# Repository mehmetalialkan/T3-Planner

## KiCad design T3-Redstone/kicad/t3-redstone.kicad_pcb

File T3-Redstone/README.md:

# T3-Redstone

**T3 Gemstone O1 için ROS 2 mobil robot kontrol kartı.**
Gazebo ile aynı yazılımı çalıştıran, TurtleBot sınıfı bir platform.

## Neden

Gemstone O1 güçlü bir bilgisayar ama robot yapmak için üç şeyi yok:

| Eksik | Sonuç |
|---|---|
| **Hiç ADC yok** | Analog sensör, batarya izleme, potansiyometre imkânsız |
| **Motor güç katı yok** | Her takım kendi sürücüsünü breadboard'da kuruyor |
| **7 PWM, ikisi periyot-bağlı** | 50 Hz servo + 400 Hz ESC aynı çipte çalışmıyor |

Redstone bunları ekler ve motor/enkoder işini ESP32-S3'e devrederek Linux'u
gerçek zamanlı kontrol yükünden kurtarır.

## Mimari

```
Gemstone O1 (Linux, ROS 2)              Redstone (ESP32-S3)
├── Nav2 / slam_toolbox                 ├── Tekerlek PID hiz kontrolu
├── ros2_control                        ├── Enkoder sayimi (PCNT, donanim)
│   └── RedstoneHardware ──UART──────>  ├── 16 kanal servo (PCA9685)
├── IMU: ICM-20948 (kartta zaten var)   ├── Batarya izleme (INA226)
└── LiDAR: RPLIDAR USB                  └── Acil stop + watchdog
```

**Kartta zaten olanı tekrar etmiyoruz:** IMU, barometre, RTC, CAN, Wi-Fi/BT,
fan sürücü — hepsi Gemstone'un üstünde.

## Gazebo uyumluluğu

Tek `use_sim` argümanıyla geçiş. Üstteki hiçbir katman değişmez:

```
use_sim:=false -> RedstoneHardware (SystemInterface) -> UART -> ESP32
use_sim:=true  -> gz_ros2_control/GazeboSimSystem    -> Gazebo
```

Aynı URDF, aynı `controllers.yaml`, aynı launch:
`diff_drive_controller` (`/cmd_vel` → `/odom` + TF), `joint_state_broadcaster`.

## Mekanik

Gemstone O1'in kendi Fritzing dosyasından ölçüldü — **Raspberry Pi Model B
form faktörü**:

| | Gemstone O1 | Redstone |
|---|---|---|
| Boyut | 85.0 × 56.0 mm | **85.0 × 56.0 mm** (tam boy) |
| Köşe | 3.0 mm | 3.0 mm |
| Delikler | 58 × 49 mm, sol kenardan 3.5 mm | aynı |
| Header | 2×20 erkek | **2×20 dişi soket, yüksek** |

### Kamera / DSI kesiti
Alt kenara açık bir U kesit: FPC kablosu dışarı çıkar, mandala parmak girer,
frezelemesi kolaydır. Şu anki değer `X 40→57 mm, derinlik 14 mm`.
**Bu değerler fotoğraftan tahmin edildi — Gemstone'un J4 (CSI) ve J12 (CSI/DSI)
konnektörlerini kumpasla ölç**, `kicad/rs_design.py` içindeki `CUT` sözlüğünü
güncelle ve `make` ile kartı yeniden üret.

### Yüksek header zorunlu
Tam boy shield, Gemstone'un **USB-A yığını ve RJ45'inin üzerinden geçer**
(~13.5 mm). Bu yüzden 2×20 dişi soket **en az 16 mm geçiş yüksekliğinde**
olmalı ve standoff'lar da aynı boyda seçilmeli. Shield'in ALT yüzeyine
komponent konulmaz.

## Güç — 2S LiPo, kartta buck yok

Gemstone'un DC girişi zaten regülatörlü, ham batarya gerilimini yiyor.
Redstone sadece **sigorta + ters polarite koruması + acil stop ayrımı + servo BEC**
yapar. Ayrıntı: [docs/03-guc-mimarisi.md](docs/03-guc-mimarisi.md)

> ⚠ Gemstone'un DC giriş aralığı iki kaynakta farklı yazıyor (5–12 V vs 5–9 V).
> Çözülene kadar **yalnızca 2S (6.0–8.4 V)** — her iki okumada da güvenli.

## Dosyalar

| Yol | İçerik |
|---|---|
| `kicad/t3-redstone.kicad_pcb` | **Kart** — 4 katman, kırmızı maske, ENIG, yerleşim + güç + sinyal yolları + GND dolgu |
| `kicad/t3-redstone.kicad_sch` | **Şema** — `rs_design.py`'den üretilir, netlist kartla pin pin aynı |
| `kicad/rs_design.py` | **Tek kaynak**: parçalar, footprint'ler, pad → net, yerleşim, güç dağıtımı |
| `kicad/rs_build.py` | Kartı KiCad'in `pcbnew` API'siyle kurar (resmi kütüphane footprint'leri) |
| `kicad/rs_route.py` | Freerouting ile yönlendirme, güç fanout'u, GND dikiş viaları, dolgu, kalan kopuklar için labirent yönlendirici, KiCad DRC |
| `kicad/rs_sch.py` | Şemayı üretir; `--check` şemadan netlist çıkarıp tasarımla karşılaştırır |
| `kicad/rs_bom.py` · `rs_docs.py` · `rs_render.py` | BOM, netlist belgesi, önizleme SVG |
| `kicad/T3RS.pretty` · `T3RS.kicad_sym` | Projeye özel footprint (servo 3×8) ve semboller (DRV8874, servo) |
| `mekanik/t3-redstone-preview.svg` · `.png` | Kartın üstten görünümü (kicad-cli) |
| `mekanik/t3-redstone-outline.dxf` | Kontur + delikler (her CAD'e girer) |
| `bom/bom.csv` | Parça listesi, MPN'li — `rs_design.py`'den üretilir |
| `docs/01-gemstone-o1-analiz.md` | Gemstone O1 donanım analizi, 40-pin tablosu, EQEP, PWM tuzağı |
| `docs/02-pin-plani.md` | Host + ESP32 pin atamaları, I2C adres haritası |
| `docs/03-guc-mimarisi.md` | Güç topolojisi, acil stop zinciri, katman dağılımı |
| `docs/04-netlist.md` | Bütün netlerin bağlantı listesi + pinout doğrulama tablosu (üretilir) |
| `docs/05-revB-degisiklikler.md` | **Rev A'da bulunan hatalar ve düzeltmeler** |

### Yeniden üretmek

```bash
cd kicad
make            # rs_build -> rs_route -> rs_sch --check -> BOM / netlist / önizleme
```

KiCad 7 (`pcbnew` Python modülüyle), Java 25+ ve Freerouting 2.4.1 gerekir
(`FREEROUTING_JAR=...`, Maven Central: `app.freerouting:freerouting:2.4.1`, `-executable.jar`).
Bir pin ya da koordinat değiştirmek için yalnızca `rs_design.py`'yi düzenle.
Dosyalar KiCad 7 biçiminde üretilir; KiCad 8 / 9 açar.

Freerouting her çalıştırmada biraz farklı yol çizer; `rs_route.py` kalan kopuk parçaları
kendi küçük yönlendiricisiyle tamamlar ve sonunda KiCad DRC'yi çalıştırır
(`kicad/build/drc.rpt`). `python3 rs_route.py --no-route` son Freerouting sonucunu
(`build/t3-redstone.ses`) yeniden kullanır — yerleşim değişmediyse aynı kartı birebir üretir.

## Kartın durumu (rev B)

**Bitmiş olanlar**
- Bütün entegre pinleri resmi kütüphaneyle / veri sayfasıyla karşılaştırıldı; rev A'daki
  14 kritik hata düzeltildi — liste: [docs/05-revB-degisiklikler.md](docs/05-revB-degisiklikler.md)
- 87 komponent (resmi KiCad footprint'leri), 85 net; yerleşim çakışmasız
- 4 katman: `F.Cu` sinyal + güç dökümleri · `In1.Cu` kesintisiz GND · `In2.Cu` bölünmüş güç
  (VSYS / +5V / +3V3 / VBAT_SW) · `B.Cu` sinyal + GND dolgu
- **Kart tamamen yönlendirildi — KiCad DRC: 0 ihlal, 0 bağlantısız ped, 0 footprint hatası**
  (ipek baskı ve kenar açıklıkları dahil); GND dikiş viaları, F/B GND dolgu
- Dekuplaj kondansatörleri pinlerin yanında: C2 (LDO çıkışı) ve C4 (ESP32 3V3) yönleri,
  C12 (PCA9685) konumu düzeltildi
- +3V3: solda In2 düzlemi, orta ve sağdaki tüketicilere B.Cu omurgası
- Şema üretildi; şemadan çıkan netlist kartla **pin pin aynı**
- Kırmızı lehim maskesi + ENIG stackup'ta tanımlı

**Kalan iş**
- Sipariş öncesi "Doğrulanacaklar" listesi (aşağıda) — özellikle 40-pin header ve montaj
  deliği konumları kumpasla teyit edilmeden üretime gönderme
- KiCad 8/9'da açıp bir kez gözle kontrol + Gerber / delik / CPL çıktıları

## Güç topolojisi

```
XT60 -> F1 -> Q1 ters polarite -> RS1 shunt (INA226) -> VSYS
                                                        |
                    +-------------------+---------------+-----------------+
                    |                   |                                 |
               J3 klemens         U7 5V BEC 3A                     Q2 ACIL STOP
               (Gemstone)          |       |                            |
                              servo rayı  U6 3V3 LDO           VBAT_SW -> DRV8874 x2
                              LED, enkoder  -> ESP32, mantık
```

Q2 arızada **kapalıdır**: gate VSYS'e pull-up'lı. Motorlar ancak ESP32 Q3'ü sürerken
**ve** J12'deki NC acil stop butonu kapalıyken güç alır. Ayrıntı:
[docs/03-guc-mimarisi.md](docs/03-guc-mimarisi.md).

## Doğrulanacaklar (sipariş öncesi)

1. **Gemstone DC giriş aralığı** — 5–9 V mı 5–12 V mi? (T3'e sor / e-fuse MPN'ine bak)
2. **40-pin header konumu** — el yapımı Fritzing parçasından ölçüldü, kumpasla teyit et
3. **Montaj delikleri** — layout PDF'inde MH1..MH7 var, Fritzing sadece 4'ünü çiziyor
4. **Stacking header yüksekliği** — Gemstone'un üst yüzeyindeki en yüksek eleman ölçülmeli
5. **Kamera kesiti** — `CUT` değerleri fotoğraftan tahmin
6. **DRV8874 pinout'u** — KiCad kütüphanesinde yok; TI veri sayfasıyla bir kez daha karşılaştır
7. **XT60 cinsiyeti** — kart tarafı bataryanın fişinin karşılığı olmalı (BOM: dişi)

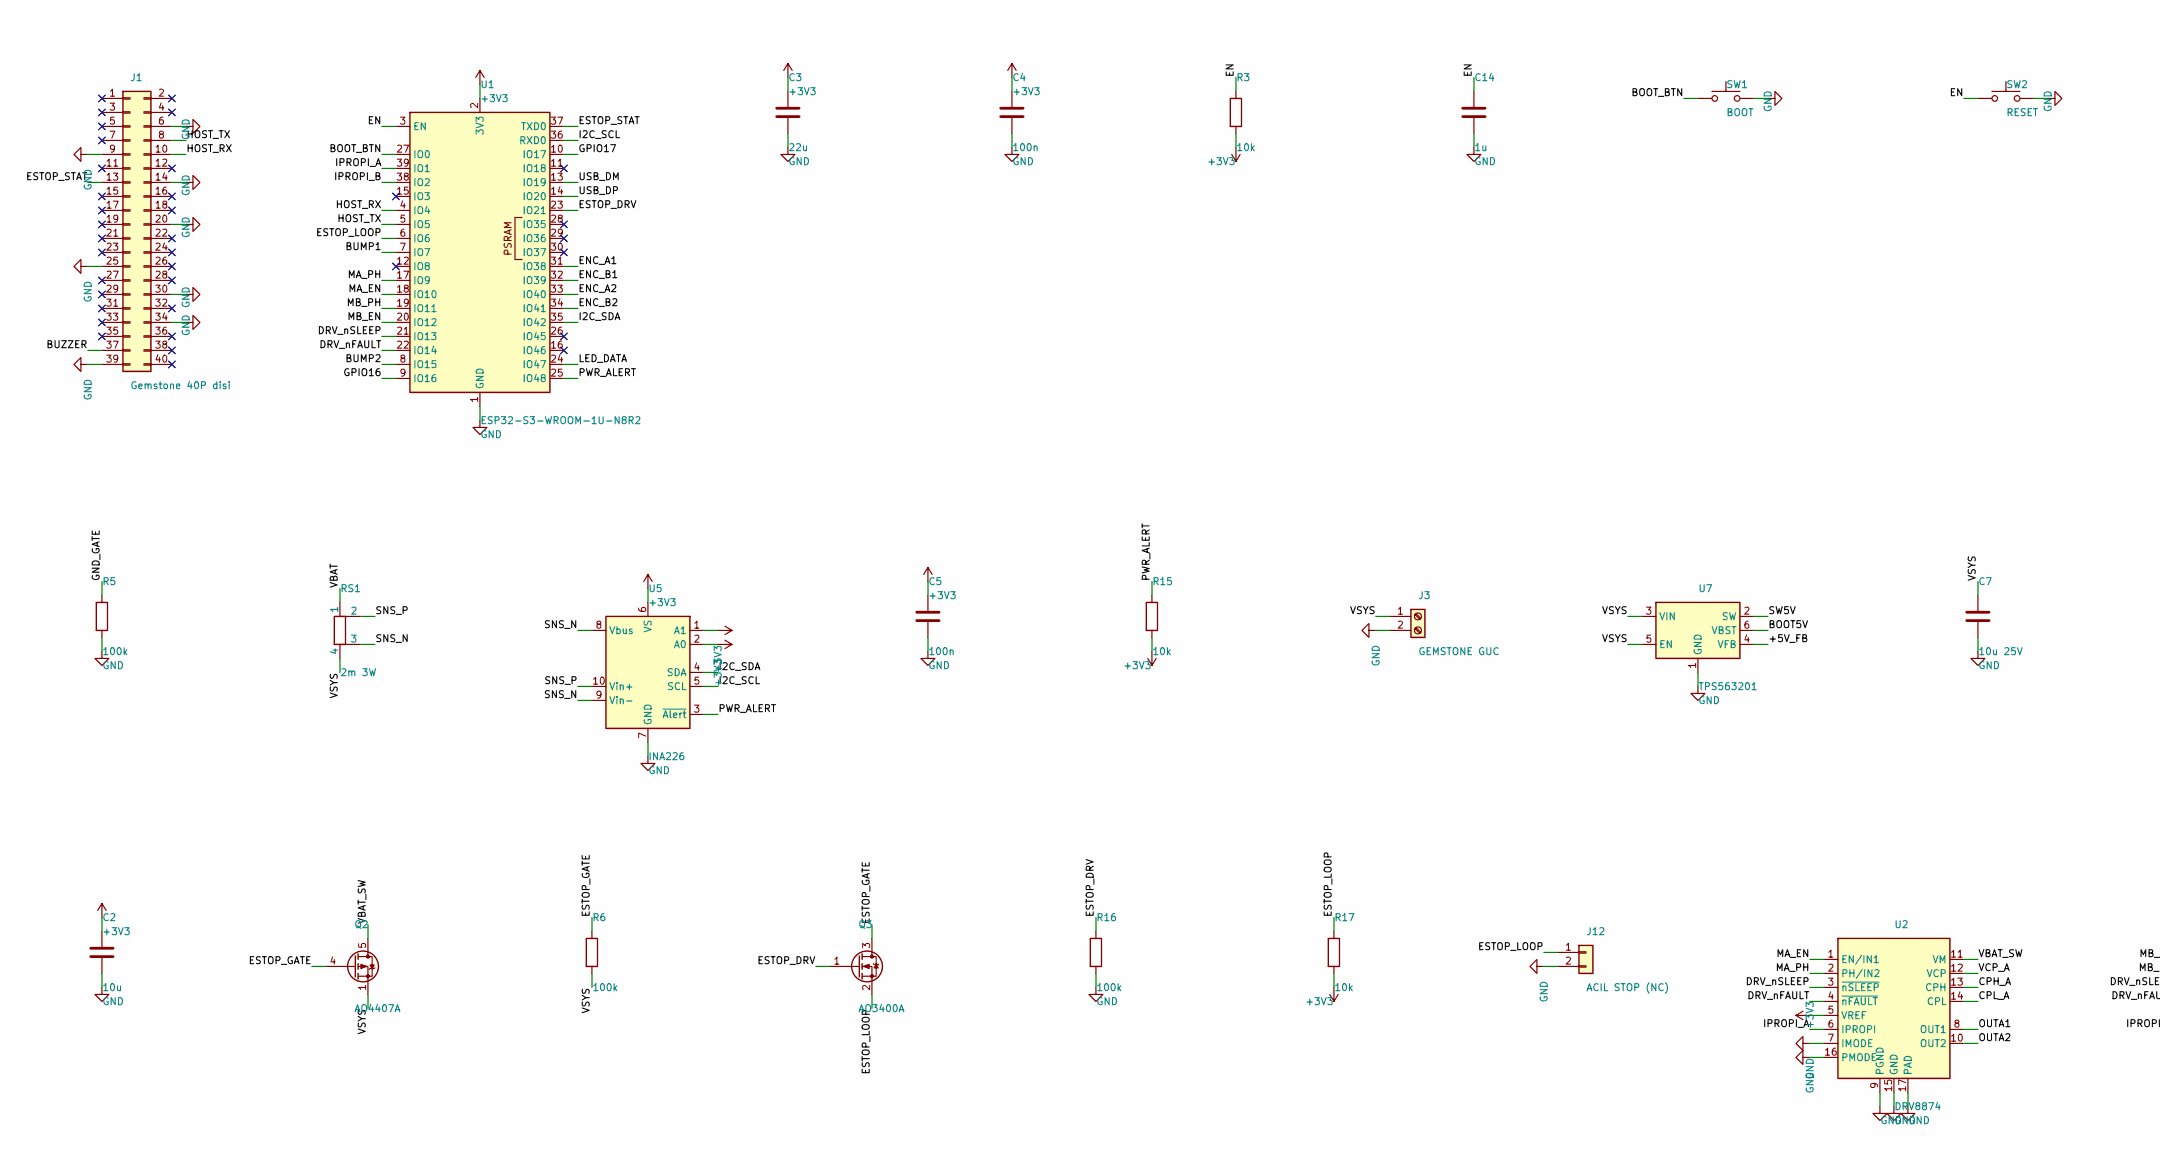
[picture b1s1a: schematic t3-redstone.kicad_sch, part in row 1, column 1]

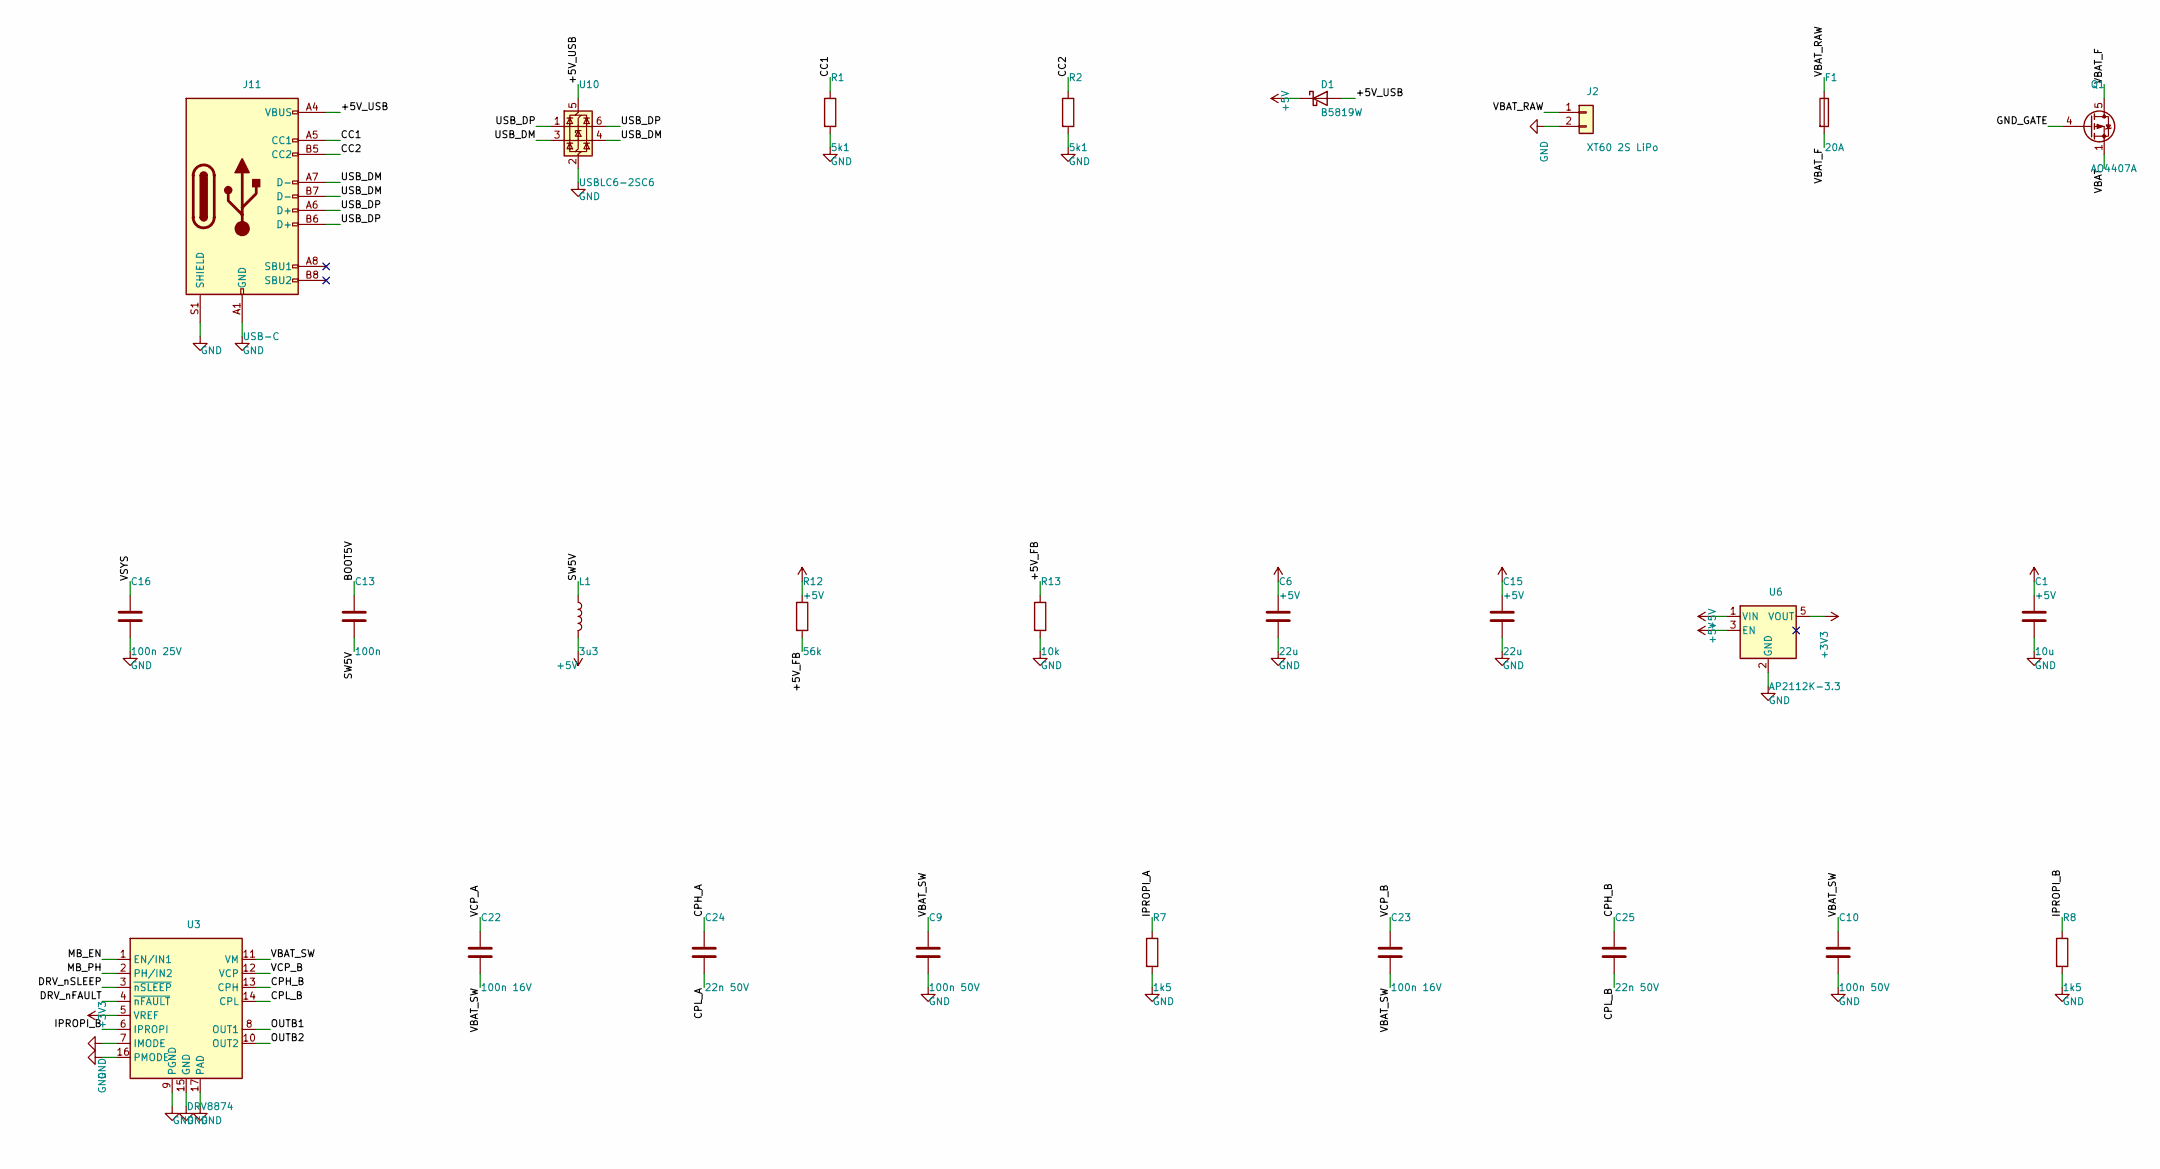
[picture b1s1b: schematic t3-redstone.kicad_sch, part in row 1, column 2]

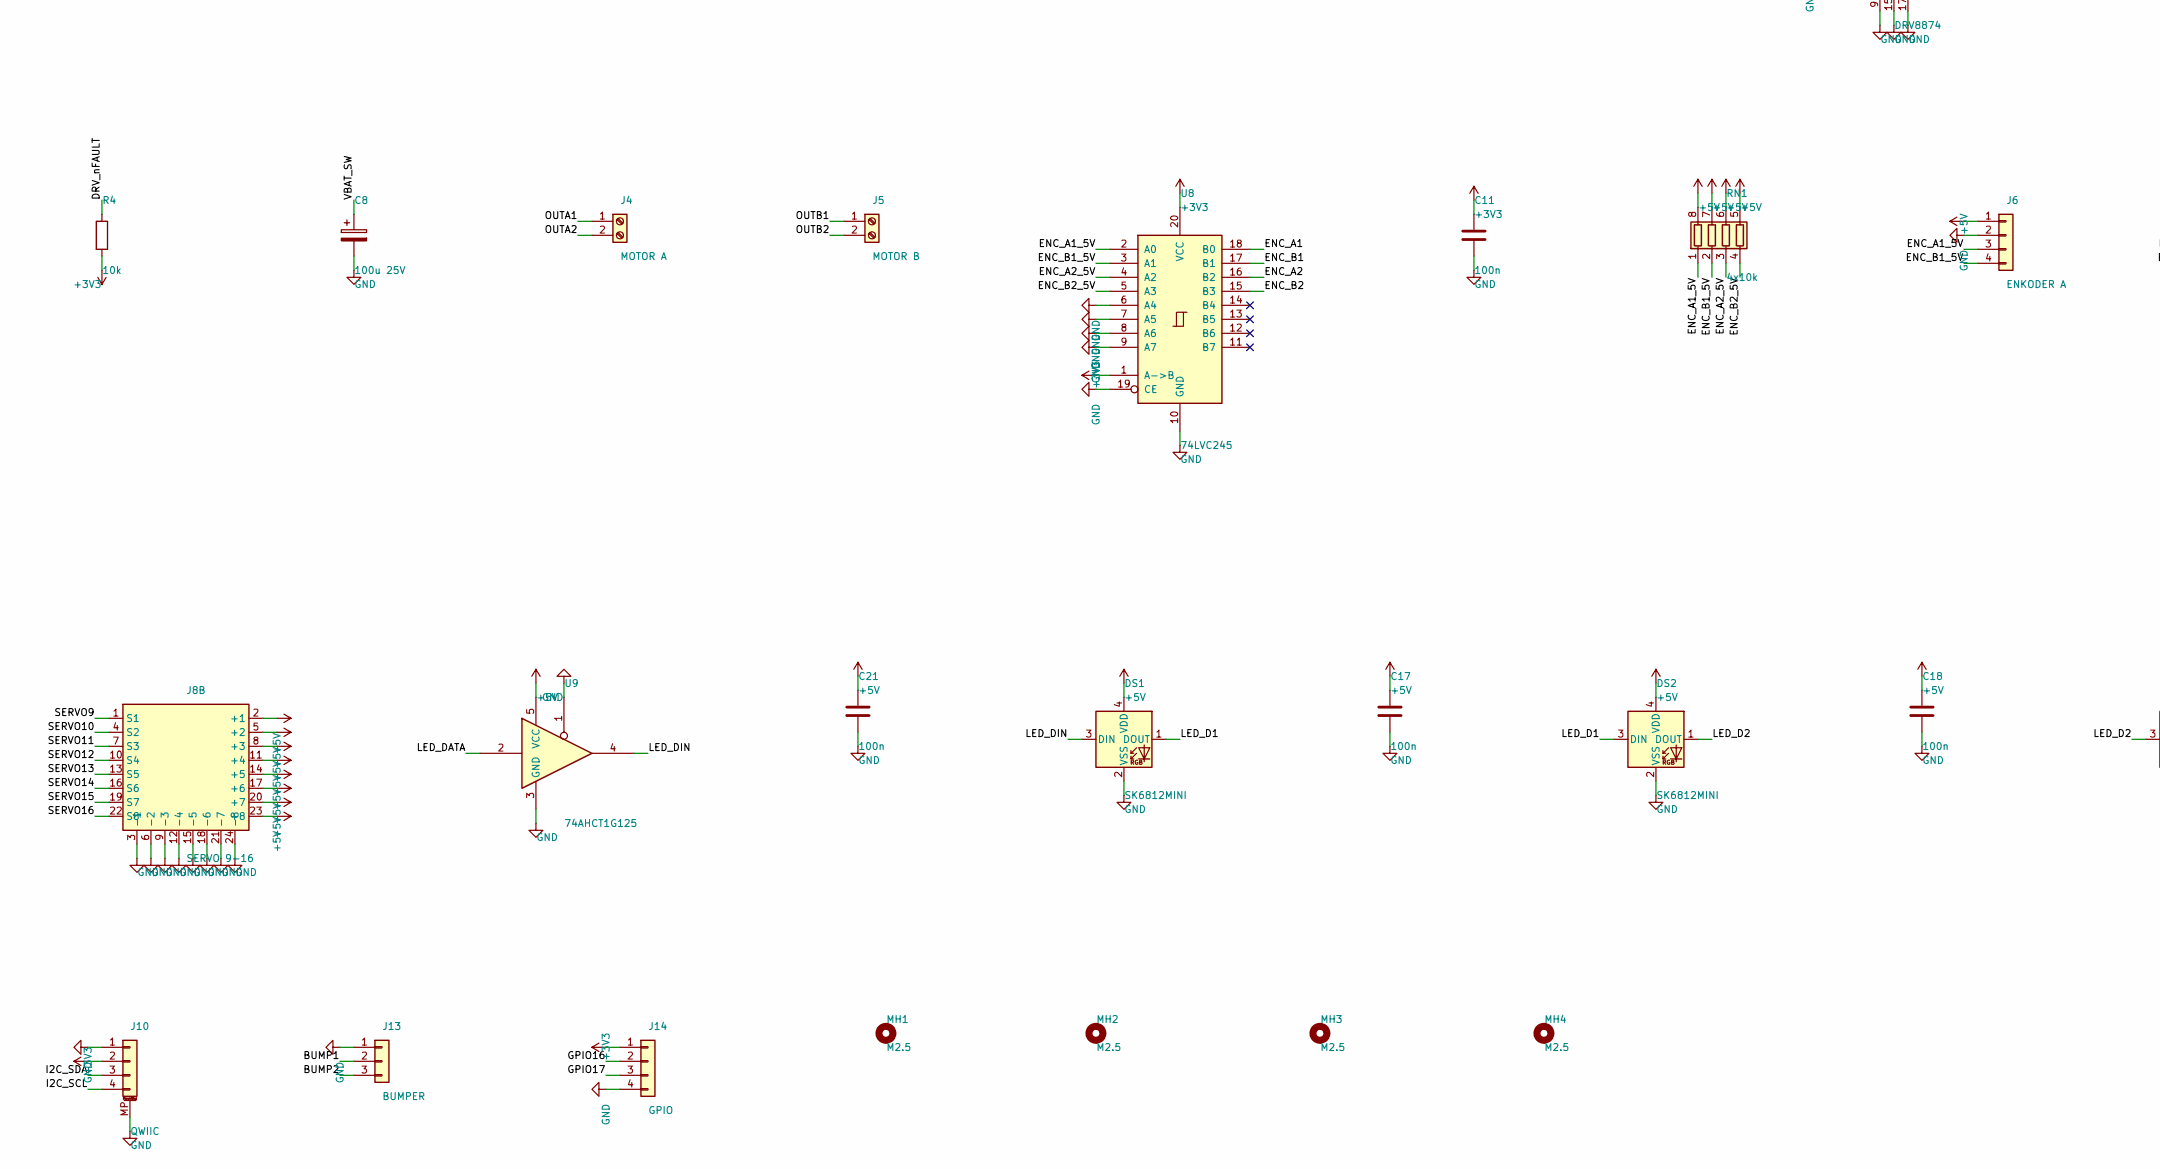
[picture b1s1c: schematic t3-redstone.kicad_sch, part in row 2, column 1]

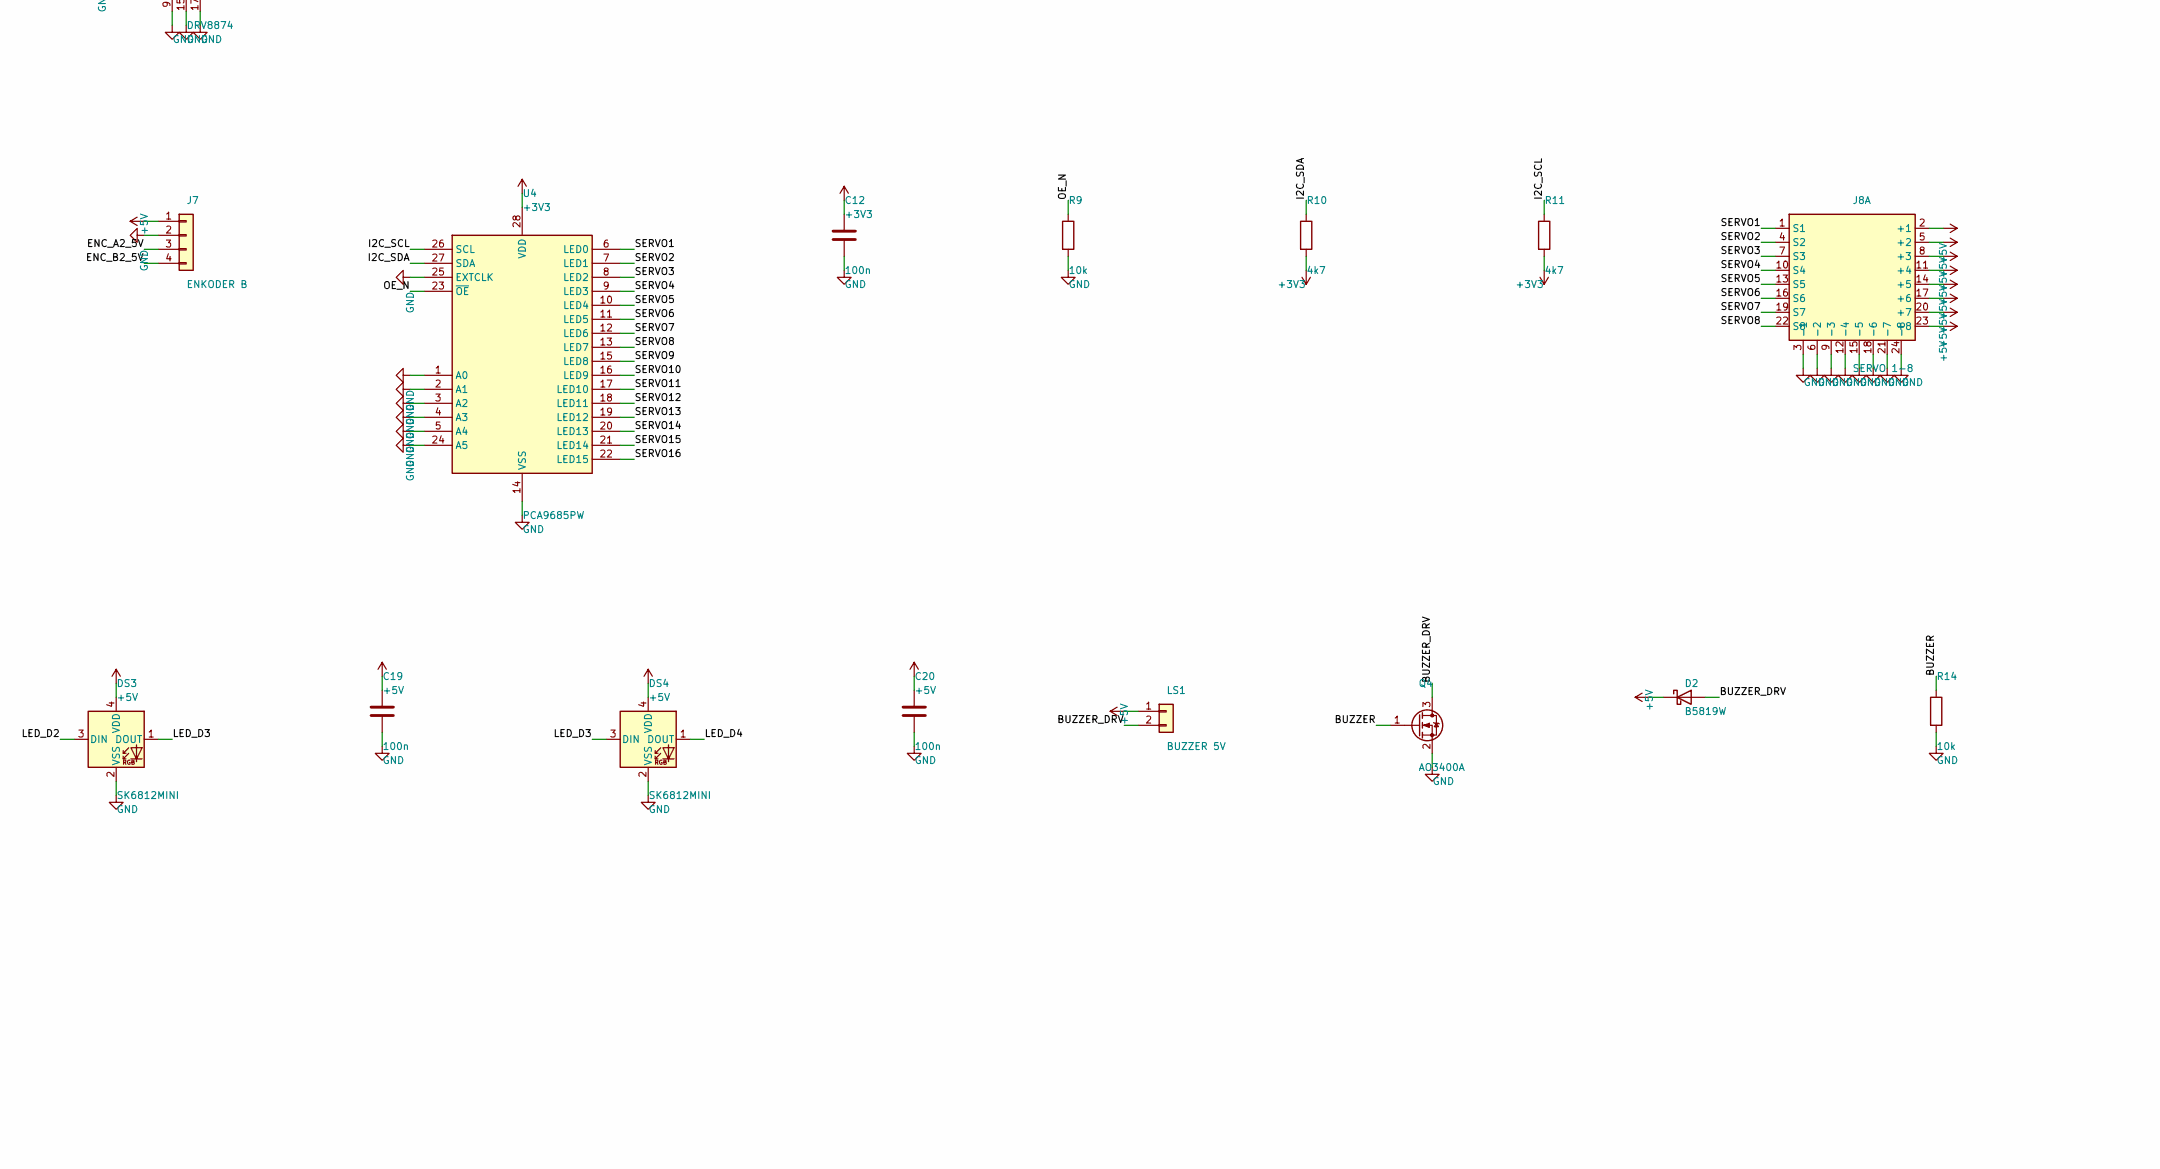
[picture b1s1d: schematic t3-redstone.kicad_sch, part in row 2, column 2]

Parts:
C1, C2: 10u; C_0805_2012Metric
C3, C6, C15: 22u; C_0805_2012Metric
C4, C5, C11, C12, C13, C17, C18, C19, C20, C21: 100n; C_0603_1608Metric
C7: 10u 25V; C_0805_2012Metric
C8: 100u 25V; CP_Elec_6.3x7.7; MPN EEE-FK1E101P
C9, C10: 100n 50V; C_0402_1005Metric
C14: 1u; C_0603_1608Metric
C16: 100n 25V; C_0603_1608Metric
C22, C23: 100n 16V; C_0402_1005Metric
C24, C25: 22n 50V; C_0402_1005Metric
D1, D2: B5819W; D_SOD-123; MPN B5819W
DS1, DS2, DS3, DS4: SK6812MINI; LED_SK6812MINI_PLCC4_3.5x3.5mm_P1.75mm; MPN SK6812MINI
F1: 20A; Fuse_2512_6332Metric; MPN Bel Fuse 0685P/2512 20A
J1: Gemstone 40P disi; PinSocket_2x20_P2.54mm_Vertical; MPN 2x20 disi, >=16mm gecis (stacking)
J2: XT60 2S LiPo; AMASS_XT60-F_1x02_P7.20mm_Vertical; MPN AMASS XT60-F
J3: GEMSTONE GUC; TerminalBlock_bornier-2_P5.08mm; MPN KF301-2P 5.08
J4: MOTOR A; TerminalBlock_bornier-2_P5.08mm; MPN KF301-2P 5.08
J5: MOTOR B; TerminalBlock_bornier-2_P5.08mm; MPN KF301-2P 5.08
J6: ENKODER A; JST_XH_B4B-XH-A_1x04_P2.50mm_Vertical; MPN JST B4B-XH-A
J7: ENKODER B; JST_XH_B4B-XH-A_1x04_P2.50mm_Vertical; MPN JST B4B-XH-A
J8A: SERVO 1-8; Servo_3x08_P2.54mm; MPN 3x8 erkek header 2.54
J8B: SERVO 9-16; Servo_3x08_P2.54mm; MPN 3x8 erkek header 2.54
J10: QWIIC; JST_SH_SM04B-SRSS-TB_1x04-1MP_P1.00mm_Horizontal; MPN JST SM04B-SRSS-TB
J11: USB-C; USB_C_Receptacle_GCT_USB4105-xx-A_16P_TopMnt_Horizontal; MPN GCT USB4105-GF-A
J12: ACIL STOP (NC); JST_XH_B2B-XH-A_1x02_P2.50mm_Vertical; MPN JST B2B-XH-A
J13: BUMPER; JST_XH_B3B-XH-A_1x03_P2.50mm_Vertical; MPN JST B3B-XH-A
J14: GPIO; PinHeader_1x04_P2.54mm_Vertical; MPN 1x4 erkek 2.54
L1: 3u3; L_Sunlord_SWPA5040S; MPN SWPA5040S3R3MT
LS1: BUZZER 5V; JST_XH_B2B-XH-A_1x02_P2.50mm_Vertical; MPN JST B2B-XH-A
MH1, MH2, MH3, MH4: M2.5; MountingHole_2.7mm_M2.5
Q1, Q2: AO4407A; SOIC-8_3.9x4.9mm_P1.27mm; MPN AO4407A
Q3, Q4: AO3400A; SOT-23; MPN AO3400A
R1, R2: 5k1; R_0603_1608Metric
R3, R4, R9, R13, R14, R15, R17: 10k; R_0603_1608Metric
R5, R6, R16: 100k; R_0603_1608Metric
R7, R8: 1k5; R_0603_1608Metric
R10, R11: 4k7; R_0603_1608Metric
R12: 56k; R_0603_1608Metric
RN1: 4x10k; R_Array_Convex_4x0603; MPN CAY16-103J4LF
RS1: 2m 3W; R_Shunt_Vishay_WSK2512_6332Metric_T1.19mm; MPN Vishay WSK2512 2mOhm
SW1: BOOT; SW_SPST_PTS810; MPN PTS810 SJM 250 SMTR LFS
SW2: RESET; SW_SPST_PTS810; MPN PTS810 SJM 250 SMTR LFS
U1: ESP32-S3-WROOM-1U-N8R2; ESP32-S3-WROOM-1U; MPN ESP32-S3-WROOM-1U-N8R2
U2, U3: DRV8874; HTSSOP-16-1EP_4.4x5mm_P0.65mm_EP3.4x5mm_Mask2.46x2.31mm_The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; MPN DRV8874PWPR
U4: PCA9685PW; TSSOP-28_4.4x9.7mm_P0.65mm; MPN PCA9685PW
U5: INA226; VSSOP-10_3x3mm_P0.5mm; MPN INA226AIDGSR
U6: AP2112K-3.3; SOT-23-5; MPN AP2112K-3.3TRG1
U7: TPS563201; SOT-23-6; MPN TPS563201DDCR
U8: 74LVC245; TSSOP-20_4.4x6.5mm_P0.65mm; MPN SN74LVC245APWR
U9: 74AHCT1G125; SOT-23-5; MPN SN74AHCT1G125DBVR
U10: USBLC6-2SC6; SOT-23-6; MPN USBLC6-2SC6

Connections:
+3V3: C2.1, C3.1, C4.1, C5.1, C11.1, C12.1, J10.2, J14.1, R3.2, R4.2, R10.2, R11.2, R15.2, R17.2, U1.2 (3V3), U2.5 (VREF), U3.5 (VREF), U4.28 (VDD), U5.1 (A1), U5.2 (A0), U5.6 (VS), U6.5 (VOUT), U8.1 (A->B), U8.20 (VCC)
+5V: C1.1, C6.1, C15.1, C17.1, C18.1, C19.1, C20.1, C21.1, D1.1 (K), D2.1 (K), DS1.4 (VDD), DS2.4 (VDD), DS3.4 (VDD), DS4.4 (VDD), J6.1, J7.1, J8A.2 (+1), J8A.5 (+2), J8A.8 (+3), J8A.11 (+4), J8A.14 (+5), J8A.17 (+6), J8A.20 (+7), J8A.23 (+8), J8B.2 (+1), J8B.5 (+2), J8B.8 (+3), J8B.11 (+4), J8B.14 (+5), J8B.17 (+6), J8B.20 (+7), J8B.23 (+8), L1.2, LS1.1, R12.1, RN1.5 (R4.2), RN1.6 (R3.2), RN1.7 (R2.2), RN1.8 (R1.2), U6.1 (VIN), U6.3 (EN), U9.5 (VCC)
+5V_FB: R12.2, R13.1, U7.4 (VFB)
+5V_USB: D1.2 (A), J11.A4 (VBUS), J11.A9 (VBUS), J11.B4 (VBUS), J11.B9 (VBUS), U10.5 (VBUS)
BOOT5V: C13.1, U7.6 (VBST)
BOOT_BTN: SW1.1, U1.27 (IO0)
BUMP1: J13.2, U1.7 (IO7)
BUMP2: J13.3, U1.8 (IO15)
BUZZER: J1.37, Q4.1 (G), R14.1
BUZZER_DRV: D2.2 (A), LS1.2, Q4.3 (D)
CC1: J11.A5 (CC1), R1.1
CC2: J11.B5 (CC2), R2.1
CPH_A: C24.1, U2.13 (CPH)
CPH_B: C25.1, U3.13 (CPH)
CPL_A: C24.2, U2.14 (CPL)
CPL_B: C25.2, U3.14 (CPL)
DRV_nFAULT: R4.1, U1.22 (IO14), U2.4 (~nFAULT), U3.4 (~nFAULT)
DRV_nSLEEP: U1.21 (IO13), U2.3 (~nSLEEP), U3.3 (~nSLEEP)
EN: C14.1, R3.1, SW2.1, U1.3 (EN)
ENC_A1: U1.31 (IO38), U8.18 (B0)
ENC_A1_5V: J6.3, RN1.1 (R1.1), U8.2 (A0)
ENC_A2: U1.33 (IO40), U8.16 (B2)
ENC_A2_5V: J7.3, RN1.3 (R3.1), U8.4 (A2)
ENC_B1: U1.32 (IO39), U8.17 (B1)
ENC_B1_5V: J6.4, RN1.2 (R2.1), U8.3 (A1)
ENC_B2: U1.34 (IO41), U8.15 (B3)
ENC_B2_5V: J7.4, RN1.4 (R4.1), U8.5 (A3)
ESTOP_DRV: Q3.1 (G), R16.1, U1.23 (IO21)
ESTOP_GATE: Q2.4 (G), Q3.3 (D), R6.1
ESTOP_LOOP: J12.1, Q3.2 (S), R17.1, U1.6 (IO6)
ESTOP_STAT: J1.13, U1.37 (TXD0)
GND: C1.2, C2.2, C3.2, C4.2, C5.2, C6.2, C7.2, C8.2, C9.2, C10.2, C11.2, C12.2, C14.2, C15.2, C16.2, C17.2, C18.2, C19.2, C20.2, C21.2, DS1.2 (VSS), DS2.2 (VSS), DS3.2 (VSS), DS4.2 (VSS), J1.6, J1.9, J1.14, J1.20, J1.25, J1.30, J1.34, J1.39, J2.2, J3.2, J6.2, J7.2, J8A.3 (-1), J8A.6 (-2), J8A.9 (-3), J8A.12 (-4), J8A.15 (-5), J8A.18 (-6), J8A.21 (-7), J8A.24 (-8), J8B.3 (-1), J8B.6 (-2), J8B.9 (-3), J8B.12 (-4), J8B.15 (-5), J8B.18 (-6), J8B.21 (-7), J8B.24 (-8), J10.1, J10.MP (MountPin), J11.A1 (GND), J11.A12 (GND), J11.B1 (GND), J11.B12 (GND), J11.S1 (SHIELD), J12.2, J13.1, J14.4, Q4.2 (S), R1.2, R2.2, R5.2, R7.2, R8.2, R9.2, R13.2, R14.2, R16.2, SW1.2, SW2.2, U1.1 (GND), U1.40 (GND), U1.41 (GND), U2.7 (IMODE), U2.9 (PGND), U2.15 (GND), U2.16 (PMODE), U2.17 (PAD), U3.7 (IMODE), U3.9 (PGND), U3.15 (GND), U3.16 (PMODE), U3.17 (PAD), U4.1 (A0), U4.2 (A1), U4.3 (A2), U4.4 (A3), U4.5 (A4), U4.14 (VSS), U4.24 (A5), U4.25 (EXTCLK), U5.7 (GND), U6.2 (GND), U7.1 (GND), U8.6 (A4), U8.7 (A5), U8.8 (A6), U8.9 (A7), U8.10 (GND), U8.19 (CE), U9.1, U9.3 (GND), U10.2 (GND)
GND_GATE: Q1.4 (G), R5.1
GPIO16: J14.2, U1.9 (IO16)
GPIO17: J14.3, U1.10 (IO17)
HOST_RX: J1.10, U1.4 (IO4)
HOST_TX: J1.8, U1.5 (IO5)
I2C_SCL: J10.4, R11.1, U1.36 (RXD0), U4.26 (SCL), U5.5 (SCL)
I2C_SDA: J10.3, R10.1, U1.35 (IO42), U4.27 (SDA), U5.4 (SDA)
IPROPI_A: R7.1, U1.39 (IO1), U2.6 (IPROPI)
IPROPI_B: R8.1, U1.38 (IO2), U3.6 (IPROPI)
LED_D1: DS1.1 (DOUT), DS2.3 (DIN)
LED_D2: DS2.1 (DOUT), DS3.3 (DIN)
LED_D3: DS3.1 (DOUT), DS4.3 (DIN)
LED_D4: DS4.1 (DOUT)
LED_DATA: U1.24 (IO47), U9.2
LED_DIN: DS1.3 (DIN), U9.4
MA_EN: U1.18 (IO10), U2.1 (EN/IN1)
MA_PH: U1.17 (IO9), U2.2 (PH/IN2)
MB_EN: U1.20 (IO12), U3.1 (EN/IN1)
MB_PH: U1.19 (IO11), U3.2 (PH/IN2)
OE_N: R9.1, U4.23 (~OE)
OUTA1: J4.1, U2.8 (OUT1)
OUTA2: J4.2, U2.10 (OUT2)
OUTB1: J5.1, U3.8 (OUT1)
OUTB2: J5.2, U3.10 (OUT2)
PWR_ALERT: R15.1, U1.25 (IO48), U5.3 (~Alert)
SERVO1: J8A.1 (S1), U4.6 (LED0)
SERVO2: J8A.4 (S2), U4.7 (LED1)
SERVO3: J8A.7 (S3), U4.8 (LED2)
SERVO4: J8A.10 (S4), U4.9 (LED3)
SERVO5: J8A.13 (S5), U4.10 (LED4)
SERVO6: J8A.16 (S6), U4.11 (LED5)
SERVO7: J8A.19 (S7), U4.12 (LED6)
SERVO8: J8A.22 (S8), U4.13 (LED7)
SERVO9: J8B.1 (S1), U4.15 (LED8)
SERVO10: J8B.4 (S2), U4.16 (LED9)
SERVO11: J8B.7 (S3), U4.17 (LED10)
SERVO12: J8B.10 (S4), U4.18 (LED11)
SERVO13: J8B.13 (S5), U4.19 (LED12)
SERVO14: J8B.16 (S6), U4.20 (LED13)
SERVO15: J8B.19 (S7), U4.21 (LED14)
SERVO16: J8B.22 (S8), U4.22 (LED15)
SNS_N: RS1.3, U5.8 (Vbus), U5.9 (Vin-)
SNS_P: RS1.2, U5.10 (Vin+)
SW5V: C13.2, L1.1, U7.2 (SW)
USB_DM: J11.A7 (D-), J11.B7 (D-), U1.13 (IO19), U10.3 (I/O2), U10.4 (I/O2)
USB_DP: J11.A6 (D+), J11.B6 (D+), U1.14 (IO20), U10.1 (I/O1), U10.6 (I/O1)
VBAT: Q1.1 (S), Q1.2 (S), Q1.3 (S), RS1.1
VBAT_F: F1.2, Q1.5 (D), Q1.6 (D), Q1.7 (D), Q1.8 (D)
VBAT_RAW: F1.1, J2.1
VBAT_SW: C8.1, C9.1, C10.1, C22.2, C23.2, Q2.5 (D), Q2.6 (D), Q2.7 (D), Q2.8 (D), U2.11 (VM), U3.11 (VM)
VCP_A: C22.1, U2.12 (VCP)
VCP_B: C23.1, U3.12 (VCP)
VSYS: C7.1, C16.1, J3.1, Q2.1 (S), Q2.2 (S), Q2.3 (S), R6.2, RS1.4, U7.3 (VIN), U7.5 (EN)

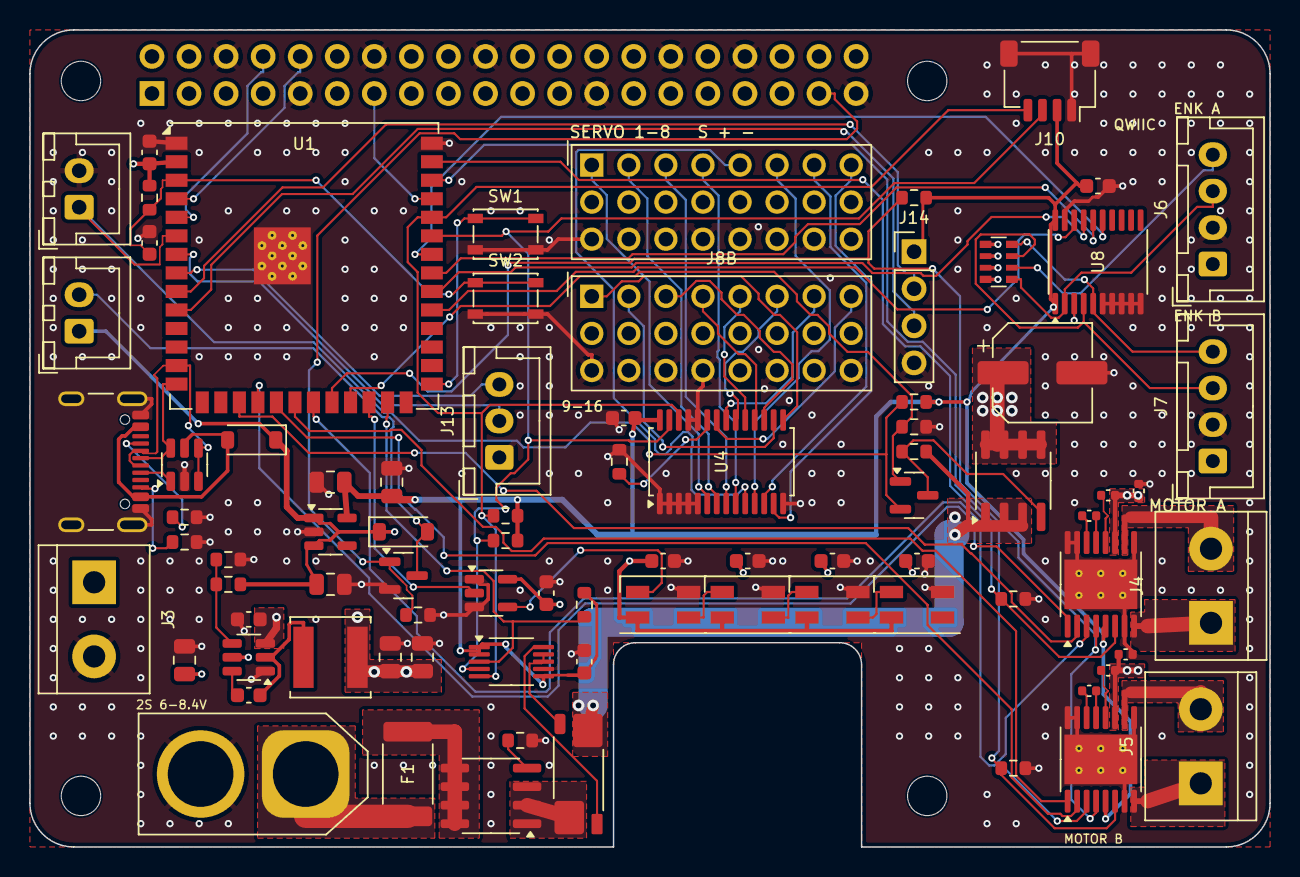
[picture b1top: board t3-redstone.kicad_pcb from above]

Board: 4 copper layers, 85.0 x 56.0 mm, 87 parts (1 on the bottom side), 84 nets.

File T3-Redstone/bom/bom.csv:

Ref,Adet,Deger,MPN,Footprint,Not,Yuz
C1 C2,2,10u,,C_0805_2012Metric,,F (ust)
C3 C6 C15,3,22u,,C_0805_2012Metric,,F (ust)
C4 C5 C11 C12 C13 C17 C18 C19 C20 C21,10,100n,,C_0603_1608Metric,,F (ust)
C7,1,10u 25V,,C_0805_2012Metric,,F (ust)
C8,1,100u 25V,EEE-FK1E101P,CP_Elec_6.3x7.7,motor bulk,F (ust)
C9 C10,2,100n 50V,,C_0402_1005Metric,VM dekuplaj,F (ust)
C14,1,1u,,C_0603_1608Metric,EN RC gecikmesi (zorunlu),F (ust)
C16,1,100n 25V,,C_0603_1608Metric,,F (ust)
C22 C23,2,100n 16V,,C_0402_1005Metric,VCP - VM,F (ust)
C24 C25,2,22n 50V,,C_0402_1005Metric,CPH - CPL,F (ust)
D1 D2,2,B5819W,B5819W,D_SOD-123,,F (ust)
DS1 DS2 DS3 DS4,4,SK6812MINI,SK6812MINI,LED_SK6812MINI_PLCC4_3.5x3.5mm_P1.75mm,,F (ust)
F1,1,20A,Bel Fuse 0685P/2512 20A,Fuse_2512_6332Metric,giris sigortasi,F (ust)
J1,1,Gemstone 40P disi,"2x20 disi, >=16mm gecis (stacking)",PinSocket_2x20_P2.54mm_Vertical,"5V pinleri (2,4) BILEREK bos",B (alt)
J2,1,XT60 2S LiPo,AMASS XT60-F,AMASS_XT60-F_1x02_P7.20mm_Vertical,6.0-8.4V; bataryanin karsiligi,F (ust)
J3,1,GEMSTONE GUC,KF301-2P 5.08,TerminalBlock_bornier-2_P5.08mm,Gemstone DC girisine pigtail,F (ust)
J4,1,MOTOR A,KF301-2P 5.08,TerminalBlock_bornier-2_P5.08mm,,F (ust)
J5,1,MOTOR B,KF301-2P 5.08,TerminalBlock_bornier-2_P5.08mm,,F (ust)
J6,1,ENKODER A,JST B4B-XH-A,JST_XH_B4B-XH-A_1x04_P2.50mm_Vertical,,F (ust)
J7,1,ENKODER B,JST B4B-XH-A,JST_XH_B4B-XH-A_1x04_P2.50mm_Vertical,,F (ust)
J8A,1,SERVO 1-8,3x8 erkek header 2.54,Servo_3x08_P2.54mm,,F (ust)
J8B,1,SERVO 9-16,3x8 erkek header 2.54,Servo_3x08_P2.54mm,,F (ust)
J10,1,QWIIC,JST SM04B-SRSS-TB,JST_SH_SM04B-SRSS-TB_1x04-1MP_P1.00mm_Horizontal,,F (ust)
J11,1,USB-C,GCT USB4105-GF-A,USB_C_Receptacle_GCT_USB4105-xx-A_16P_TopMnt_Horizontal,flaslama / konsol,F (ust)
J12,1,ACIL STOP (NC),JST B2B-XH-A,JST_XH_B2B-XH-A_1x02_P2.50mm_Vertical,NC buton; buton yoksa kopru tak,F (ust)
J13,1,BUMPER,JST B3B-XH-A,JST_XH_B3B-XH-A_1x03_P2.50mm_Vertical,,F (ust)
J14,1,GPIO,1x4 erkek 2.54,PinHeader_1x04_P2.54mm_Vertical,,F (ust)
L1,1,3u3,SWPA5040S3R3MT,L_Sunlord_SWPA5040S,Isat >= 4A,F (ust)
LS1,1,BUZZER 5V,JST B2B-XH-A,JST_XH_B2B-XH-A_1x02_P2.50mm_Vertical,harici manyetik buzzer,F (ust)
Q1 Q2,2,AO4407A,AO4407A,SOIC-8_3.9x4.9mm_P1.27mm,,F (ust)
Q3 Q4,2,AO3400A,AO3400A,SOT-23,,F (ust)
R1 R2,2,5k1,,R_0603_1608Metric,,F (ust)
R3 R4 R9 R13 R14 R15 R17,7,10k,,R_0603_1608Metric,,F (ust)
R5 R6 R16,3,100k,,R_0603_1608Metric,,F (ust)
R7 R8,2,1k5,,R_0603_1608Metric,IPROPI: 3.3V ~ 4.9A,F (ust)
R10 R11,2,4k7,,R_0603_1608Metric,,F (ust)
R12,1,56k,,R_0603_1608Metric,Vout = 0.768*(1+56/10) = 5.07V,F (ust)
RN1,1,4x10k,CAY16-103J4LF,R_Array_Convex_4x0603,,F (ust)
RS1,1,2m 3W,Vishay WSK2512 2mOhm,R_Shunt_Vishay_WSK2512_6332Metric_T1.19mm,Kelvin akim shuntu,F (ust)
SW1,1,BOOT,PTS810 SJM 250 SMTR LFS,SW_SPST_PTS810,,F (ust)
SW2,1,RESET,PTS810 SJM 250 SMTR LFS,SW_SPST_PTS810,,F (ust)
U1,1,ESP32-S3-WROOM-1U-N8R2,ESP32-S3-WROOM-1U-N8R2,ESP32-S3-WROOM-1U,N8R8 ALMA: IO35-37 kaybolur,F (ust)
U2 U3,2,DRV8874,DRV8874PWPR,HTSSOP-16-1EP_4.4x5mm_P0.65mm_EP3.4x5mm_Mask2.46x2.31mm_ThermalVias,,F (ust)
U4,1,PCA9685PW,PCA9685PW,TSSOP-28_4.4x9.7mm_P0.65mm,16 kanal servo PWM,F (ust)
U5,1,INA226,INA226AIDGSR,VSSOP-10_3x3mm_P0.5mm,I2C 0x45 (A0=A1=VS),F (ust)
U6,1,AP2112K-3.3,AP2112K-3.3TRG1,SOT-23-5,,F (ust)
U7,1,TPS563201,TPS563201DDCR,SOT-23-6,5V/3A BEC,F (ust)
U8,1,74LVC245,SN74LVC245APWR,TSSOP-20_4.4x6.5mm_P0.65mm,5V -> 3V3 tampon,F (ust)
U9,1,74AHCT1G125,SN74AHCT1G125DBVR,SOT-23-5,3V3 -> 5V veri,F (ust)
U10,1,USBLC6-2SC6,USBLC6-2SC6,SOT-23-6,USB ESD,F (ust)

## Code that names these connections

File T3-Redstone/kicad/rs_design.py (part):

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# =============================================================================
# 40-pin Gemstone soketi - govde kartin ALTINDA (B yuzu), pin 1 Gemstone'un pin 1'i
# =============================================================================
HOST = {8: "HOST_TX",       # Gemstone TXD (GPIO-14) -> ESP32 RX (IO48)
        10: "HOST_RX",      # Gemstone RXD (GPIO-15) <- ESP32 TX (IO47)
        13: "ESTOP_STAT",   # ESP32 -> host, acil stop durumu
        37: "BUZZER"}       # host -> buzzer FET
J1_GND = [6, 9, 14, 20, 25, 30, 34, 39]
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    "1": "GND", "2": "+3V3", "3": "EN",
    "4": "HOST_RX", "5": "HOST_TX",                                   # IO4=TX -> host RX, IO5=RX
    "6": "ESTOP_LOOP", "7": "BUMP1", "8": "BUMP2",                    # IO6, IO7, IO15
    "9": "GPIO16", "10": "GPIO17", "11": "", "12": "",                # IO16, IO17 (J14); IO18, IO8 bos
    "13": "USB_DM", "14": "USB_DP",                                   # IO19, IO20
    "15": "", "16": "",                                               # IO3, IO46 strap - bos
    "17": "MA_PH", "18": "MA_EN", "19": "MB_PH", "20": "MB_EN",       # IO9..IO12
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P("J13", "BUMPER", XH.format(n=3), {"1": "GND", "2": "BUMP1", "3": "BUMP2"},
  mpn="JST B3B-XH-A")
P("J14", "GPIO", "Connector_PinHeader_2.54mm:PinHeader_1x04_P2.54mm_Vertical",
  {"1": "+3V3", "2": "GPIO16", "3": "GPIO17", "4": "GND"}, mpn="1x4 erkek 2.54")

for i in range(len(HOLES)):
    P(f"MH{i + 1}", "M2.5", "MountingHole:MountingHole_2.7mm_M2.5", {})
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        _spine(o2, 0.4, (75.03, 8.86 + dy), (75.03, 10.6 + dy)),
        _spine(o2, 0.8, (75.43, 10.6 + dy), (jx, 10.6 + dy)),   # bas: VM omurgasindan 0.2+
        _spine(o2, 1.0, (jx, 10.6 + dy), (jx, j2)),
        _spine("VBAT_SW", 0.3, (74.38, 8.86 + dy), (74.38, 12.1 + dy)),
        _spine("VBAT_SW", 0.4, (74.38, 12.1 + dy), (75.95, 12.1 + dy)),
    ]


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# Freerouting dokumleri diger netler icin engel saymiyor (icinden yol geciriyor);
# sabit yollari ise engel sayar. KiCad'de dokumu guclendiren gercek bakirdir.
SPINES = [
    _spine("VBAT_RAW", 1.6, (18.9, 2.1), (25.9, 2.1)),
    _spine("VBAT_F", 1.0, (25.9, 7.9), (29.12, 7.9), (29.12, 1.59)),
    _spine("VBAT", 1.0, (34.08, 2.86), (36.97, 2.02)),
    _spine("VSYS", 0.8, (38.23, 7.98), (38.6, 9.7)),
    _spine("VSYS", 0.8, (63.4, 21.4), (64.2, 22.0), (68.03, 22.0)),
    _spine("VBAT_SW", 0.8, (65.5, 27.58), (69.31, 27.58)),
    _spine("VBAT_SW", 1.0, (66.3, 27.58), (66.3, 32.5)),
    _spine("+5V", 0.8, (22.45, 12.05), (26.9, 12.05)),
    _spine("VSYS", 0.5, (16.14, 13.95), (16.9, 15.0), (16.9, 15.75)),
] + _drv_spines(0.0, "B", *J5_PADS) + _drv_spines(12.0, "A", *J4_PADS)

POWER_TRACKS = SPINES + (
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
